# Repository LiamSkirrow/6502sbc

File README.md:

# 6502 🎉

A minimal implementation of a functional 6502-based system. It has everything that's needed to get going, including a 6522 VIA (for parallel ports/GPIO control) and a 6551 ACIA (for uart connection to a serial terminal).

## Pics
TODO, include screenshots of schematic and PCB. Can I render these automatically based on the current state of the schem/pcb in the repo?

## Memory Map
TODO

## Bootloader
ASM TODO

## Components
TODO

## Tutorial, how to get up and running
TODO, sourcing components, board bring-up, writing your own ASM snippets and loading them into ram via the bootloader+serial chip. How to write your own ISRs etc.

### Development Notes
- consider replacing zero-Ohm resistors with jumper headers, so I can place/replace them without a soldering iron
- add a jumper header to be able to switch between powering the board directly via a 5V USB cable, and an LM7805 linear reg. Three way jumper header to make it impossible to simultaneously select both options.
- rework memory map so that the ROM is only large enough to contain the minimal bootloader (+ a little extra just in case). We only need the ROM to be as large as the bootloader, since the RAM is where the user-code will be loaded into ready for execution, so minimise ROM and maximise RAM util.
  - perhaps rather than sacrifice a small but fixed amount of memory to the bootloader, why not think of a way to utilise the full 64kB RAM chip once the bootloader has completed. There would need to be some kind of dynamic bank-switching involved, possibly involving one output bit of the 6522 GPIO port to adjust the address decoding to no longer enable the ROM, instead always enabling the RAM (except obviously for when accessing the 6522/6551). So, when the bootloader completes and jumps to the starting address of the user program (in RAM), the first instructions should write to a special GPIO bit that switches out the default decode logic for another logic function that keeps the ROM disabled and RAM enabled. This way, we'd be able to utilise the full ROM space and then when its job is complete we could switch to utilising the full RAM space. So we don't need to use small, fixed regions of memory at any one time, instead using potentially the full capacity of the chip.

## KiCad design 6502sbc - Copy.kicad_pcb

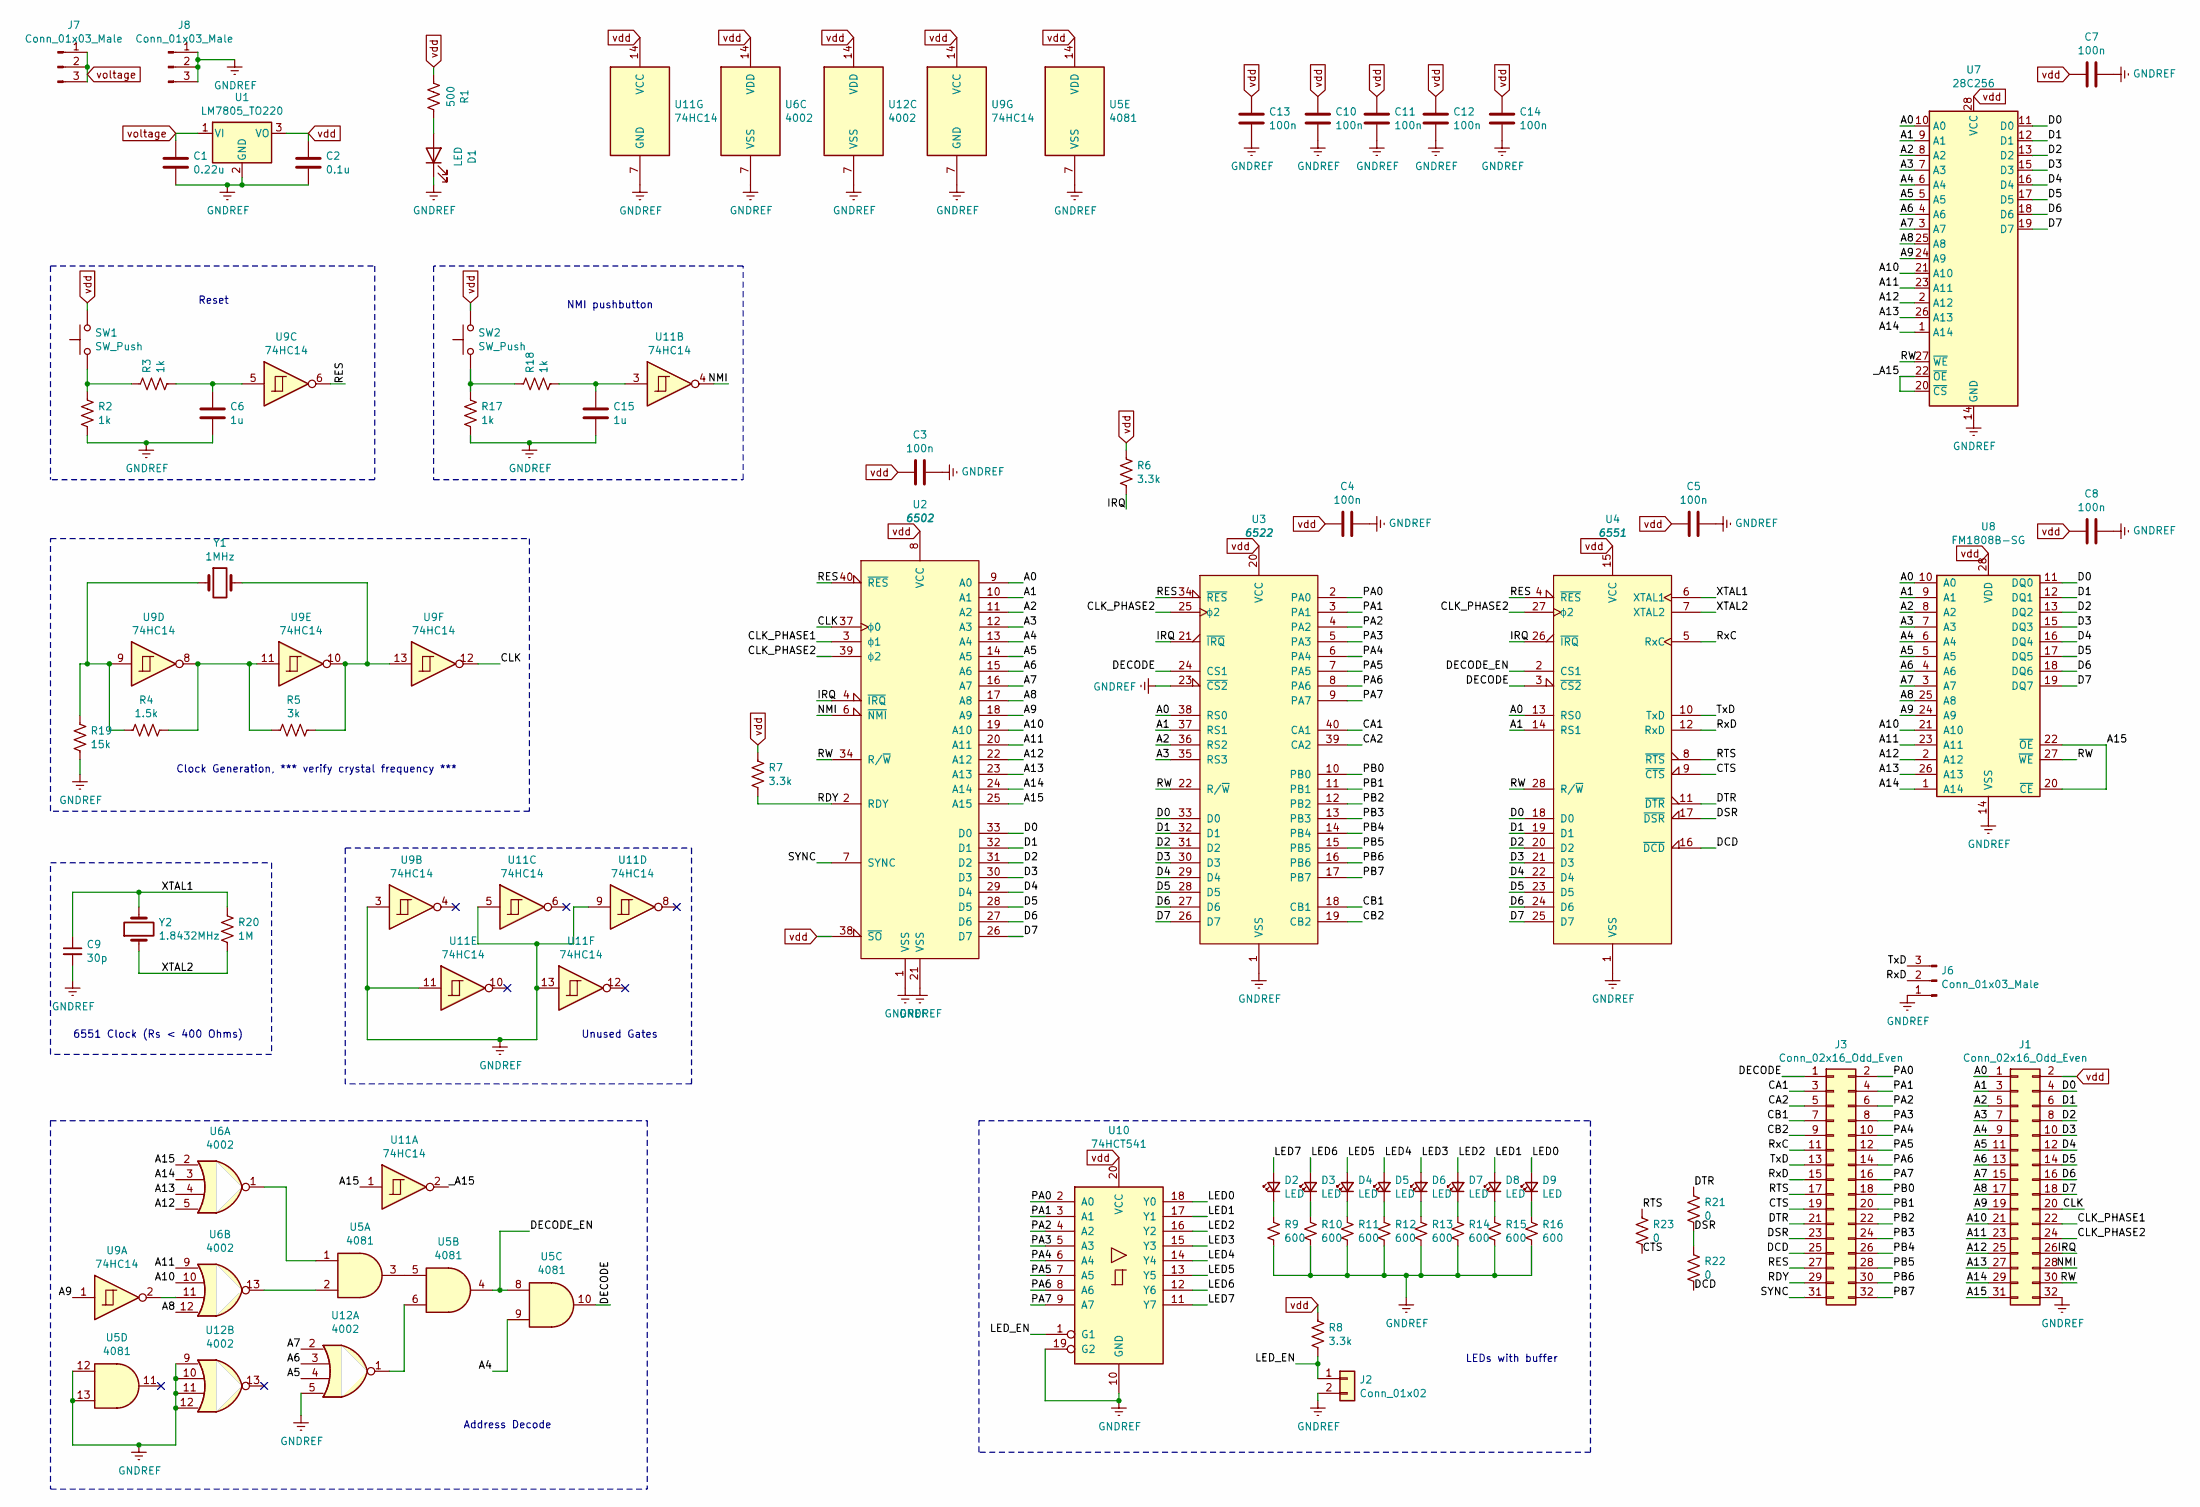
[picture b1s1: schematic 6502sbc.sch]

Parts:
C1: 0.22u; C_0805_2012Metric_Pad1.18x1.45mm_HandSolder
C2: 0.1u; C_0603_1608Metric_Pad1.08x0.95mm_HandSolder
C3, C4, C5, C7, C8, C10, C11, C12, C13, C14: 100n; C_0603_1608Metric_Pad1.08x0.95mm_HandSolder
C6, C15: 1u; C_0805_2012Metric_Pad1.18x1.45mm_HandSolder
C9: 30p; C_0805_2012Metric_Pad1.18x1.45mm_HandSolder
D1, D2, D3, D4, D5, D6, D7, D8, D9: LED; LED_0805_2012Metric_Pad1.15x1.40mm_HandSolder
J1, J3: Conn_02x16_Odd_Even; PinHeader_2x16_P2.54mm_Vertical
J2: Conn_01x02; PinHeader_1x02_P2.54mm_Vertical
J6, J7, J8: Conn_01x03_Male; PinHeader_1x03_P2.54mm_Vertical
R1: 500; R_0805_2012Metric_Pad1.20x1.40mm_HandSolder
R2, R3, R17, R18: 1k; R_0805_2012Metric_Pad1.20x1.40mm_HandSolder
R4: 1.5k; R_0805_2012Metric_Pad1.20x1.40mm_HandSolder
R5: 3k; R_0805_2012Metric_Pad1.20x1.40mm_HandSolder
R6, R7, R8: 3.3k; R_0805_2012Metric_Pad1.20x1.40mm_HandSolder
R9, R10, R11, R12, R13, R14, R15, R16: 600; R_0603_1608Metric_Pad1.05x0.95mm_HandSolder
R19: 15k; R_0805_2012Metric_Pad1.20x1.40mm_HandSolder
R20: 1M; R_0805_2012Metric_Pad1.20x1.40mm_HandSolder
R21, R22, R23: 0; R_0805_2012Metric_Pad1.20x1.40mm_HandSolder
SW1, SW2: SW_Push; SW_Push_1P1T_NO_6x6mm_H9.5mm
U1: LM7805_TO220; TO-220-3_Vertical
U2: 6502; DIP-40_W15.24mm
U3: 6522; DIP-40_W15.24mm
U4: 6551; DIP-28_W15.24mm
U5: 4081; SO-14_3.9x8.65mm_P1.27mm
U6, U12: 4002; SO-14_3.9x8.65mm_P1.27mm
U7: 28C256; DIP-28_W15.24mm
U8: FM1808B-SG; DIP-28_W15.24mm
U9, U11: 74HC14; SO-14_3.9x8.65mm_P1.27mm
U10: 74HCT541; SOIC-20W_7.5x12.8mm_P1.27mm
Y1: 1MHz; Resonator-2Pin_W6.0mm_H3.0mm
Y2: 1.8432MHz; Resonator-2Pin_W6.0mm_H3.0mm

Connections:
/A0: J1.1, U2.9 (A0), U3.38 (RS0), U4.13 (RS0), U7.10 (A0), U8.10 (A0)
/A1: J1.3, U2.10 (A1), U3.37 (RS1), U4.14 (RS1), U7.9 (A1), U8.9 (A1)
/A2: J1.5, U2.11 (A2), U3.36 (RS2), U7.8 (A2), U8.8 (A2)
/A3: J1.7, U2.12 (A3), U3.35 (RS3), U7.7 (A3), U8.7 (A3)
/A4: J1.9, U2.13 (A4), U5.9, U7.6 (A4), U8.6 (A4)
/A5: J1.11, U2.14 (A5), U7.5 (A5), U8.5 (A5), U12.4
/A6: J1.13, U2.15 (A6), U7.4 (A6), U8.4 (A6), U12.3
/A7: J1.15, U2.16 (A7), U7.3 (A7), U8.3 (A7), U12.2
/A8: J1.17, U2.17 (A8), U6.12, U7.25 (A8), U8.25 (A8)
/A9: J1.19, U2.18 (A9), U7.24 (A9), U8.24 (A9), U9.1
/A10: J1.21, U2.19 (A10), U6.10, U7.21 (A10), U8.21 (A10)
/A11: J1.23, U2.20 (A11), U6.9, U7.23 (A11), U8.23 (A11)
/A12: J1.25, U2.22 (A12), U6.5, U7.2 (A12), U8.2 (A12)
/A13: J1.27, U2.23 (A13), U6.4, U7.26 (A13), U8.26 (A13)
/A14: J1.29, U2.24 (A14), U6.3, U7.1 (A14), U8.1 (A14)
/A15: J1.31, U2.25 (A15), U6.2, U8.20 (~CE~), U8.22 (~OE~), U11.1
/CA1: J3.3, U3.40 (CA1)
/CA2: J3.5, U3.39 (CA2)
/CB1: J3.7, U3.18 (CB1)
/CB2: J3.9, U3.19 (CB2)
/CLK: J1.20, U2.37 (ϕ0), U9.12
/CLK_PHASE1: J1.22, U2.3 (ϕ1)
/CLK_PHASE2: J1.24, U2.39 (ϕ2), U3.25 (ϕ2), U4.27 (ϕ2)
/CTS: J3.19, R23.2, U4.9 (~CTS)
/D0: J1.4, U2.33 (D0), U3.33 (D0), U4.18 (D0), U7.11 (D0), U8.11 (DQ0)
/D1: J1.6, U2.32 (D1), U3.32 (D1), U4.19 (D1), U7.12 (D1), U8.12 (DQ1)
/D2: J1.8, U2.31 (D2), U3.31 (D2), U4.20 (D2), U7.13 (D2), U8.13 (DQ2)
/D3: J1.10, U2.30 (D3), U3.30 (D3), U4.21 (D3), U7.15 (D3), U8.15 (DQ3)
/D4: J1.12, U2.29 (D4), U3.29 (D4), U4.22 (D4), U7.16 (D4), U8.16 (DQ4)
/D5: J1.14, U2.28 (D5), U3.28 (D5), U4.23 (D5), U7.17 (D5), U8.17 (DQ5)
/D6: J1.16, U2.27 (D6), U3.27 (D6), U4.24 (D6), U7.18 (D6), U8.18 (DQ6)
/D7: J1.18, U2.26 (D7), U3.26 (D7), U4.25 (D7), U7.19 (D7), U8.19 (DQ7)
/DCD: J3.25, R22.2, U4.16 (~DCD)
/DECODE: J3.1, U3.24 (CS1), U4.3 (~CS2), U5.10
/DECODE_EN: U4.2 (CS1), U5.4, U5.8
/DSR: J3.23, R21.2, R22.1, U4.17 (~DSR)
/DTR: J3.21, R21.1, U4.11 (~DTR)
/IRQ: J1.26, R6.2, U2.4 (~IRQ), U3.21 (~IRQ), U4.26 (~IRQ)
/LED0: D9.2 (A), U10.18 (Y0)
/LED1: D8.2 (A), U10.17 (Y1)
/LED2: D7.2 (A), U10.16 (Y2)
/LED3: D6.2 (A), U10.15 (Y3)
/LED4: D5.2 (A), U10.14 (Y4)
/LED5: D4.2 (A), U10.13 (Y5)
/LED6: D3.2 (A), U10.12 (Y6)
/LED7: D2.2 (A), U10.11 (Y7)
/LED_EN: J2.1, R8.2, U10.1 (G1)
/NMI: J1.28, U2.6 (~NMI), U11.4
/PA0: J3.2, U3.2 (PA0), U10.2 (A0)
/PA1: J3.4, U3.3 (PA1), U10.3 (A1)
/PA2: J3.6, U3.4 (PA2), U10.4 (A2)
/PA3: J3.8, U3.5 (PA3), U10.5 (A3)
/PA4: J3.10, U3.6 (PA4), U10.6 (A4)
/PA5: J3.12, U3.7 (PA5), U10.7 (A5)
/PA6: J3.14, U3.8 (PA6), U10.8 (A6)
/PA7: J3.16, U3.9 (PA7), U10.9 (A7)
/PB0: J3.18, U3.10 (PB0)
/PB1: J3.20, U3.11 (PB1)
/PB2: J3.22, U3.12 (PB2)
/PB3: J3.24, U3.13 (PB3)
/PB4: J3.26, U3.14 (PB4)
/PB5: J3.28, U3.15 (PB5)
/PB6: J3.30, U3.16 (PB6)
/PB7: J3.32, U3.17 (PB7)
/RDY: J3.29, R7.2, U2.2 (RDY)
/RES: J3.27, U2.40 (~RES), U3.34 (~RES), U4.4 (~RES), U9.6
/RTS: J3.17, R23.1, U4.8 (~RTS)
/RW: J1.30, U2.34 (R/~W), U3.22 (R/~W), U4.28 (R/~W), U7.27 (~WE), U8.27 (~WE~)
/RxC: J3.11, U4.5 (RxC)
/RxD: J3.15, J6.2, U4.12 (RxD)
/SYNC: J3.31, U2.7 (SYNC)
/TxD: J3.13, J6.3, U4.10 (TxD)
/XTAL1: C9.1, R20.1, U4.6 (XTAL1), Y2.2
/XTAL2: R20.2, U4.7 (XTAL2), Y2.1
/_A15: U7.20 (~CS), U7.22 (~OE), U11.2
GNDREF: C1.2, C2.2, C3.1, C4.1, C5.1, C6.1, C7.1, C8.1, C9.2, C10.2, C11.2, C12.2, C13.2, C14.2, C15.1, D1.1 (K), J1.32, J2.2, J6.1, J8.1, J8.2, J8.3, R2.2, R9.2, R10.2, R11.2, R12.2, R13.2, R14.2, R15.2, R16.2, R17.2, R19.2, U1.2 (GND), U2.1 (VSS), U2.21 (VSS), U3.1 (VSS), U3.23 (~CS2), U4.1 (VSS), U5.7 (VSS), U5.12, U5.13, U6.7 (VSS), U7.14 (GND), U8.14 (VSS), U9.3, U9.7 (GND), U10.10 (GND), U10.19 (G2), U11.5, U11.7 (GND), U11.9, U11.11, U11.13, U12.5, U12.7 (VSS), U12.9, U12.10, U12.11, U12.12
unnamed: C6.2, R3.2, U9.5
unnamed: C15.2, R18.2, U11.3
unnamed: D1.2 (A), R1.1
unnamed: D2.1 (K), R9.1
unnamed: D3.1 (K), R10.1
unnamed: D4.1 (K), R11.1
unnamed: D5.1 (K), R12.1
unnamed: D6.1 (K), R13.1
unnamed: D7.1 (K), R14.1
unnamed: D8.1 (K), R15.1
unnamed: D9.1 (K), R16.1
unnamed: R2.1, R3.1, SW1.1
unnamed: R4.1, R5.2, U9.8, U9.11
unnamed: R5.1, U9.10, U9.13, Y1.2
unnamed: R17.1, R18.1, SW2.1
unnamed: R4.2, R19.1, U9.9, Y1.1
unnamed: U5.1, U6.1
unnamed: U5.2, U6.13
unnamed: U5.3, U5.5
unnamed: U6.11, U9.2
unnamed: U5.6, U12.1
vdd: C2.1, C3.2, C4.2, C5.2, C7.2, C8.2, C10.1, C11.1, C12.1, C13.1, C14.1, J1.2, R1.2, R6.1, R7.1, R8.1, SW1.2, SW2.2, U1.3 (VO), U2.8 (VCC), U2.38 (~SO), U3.20 (VCC), U4.15 (VCC), U5.14 (VDD), U6.14 (VDD), U7.28 (VCC), U8.28 (VDD), U9.14 (VCC), U10.20 (VCC), U11.14 (VCC), U12.14 (VDD)
voltage: C1.1, J7.1, J7.2, J7.3, U1.1 (VI)

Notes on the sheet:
Reset
Address Decode
Clock Generation, *** verify crystal frequency ***
6551 Clock (Rs < 400 Ohms)
LEDs with buffer
NMI pushbutton
Unused Gates

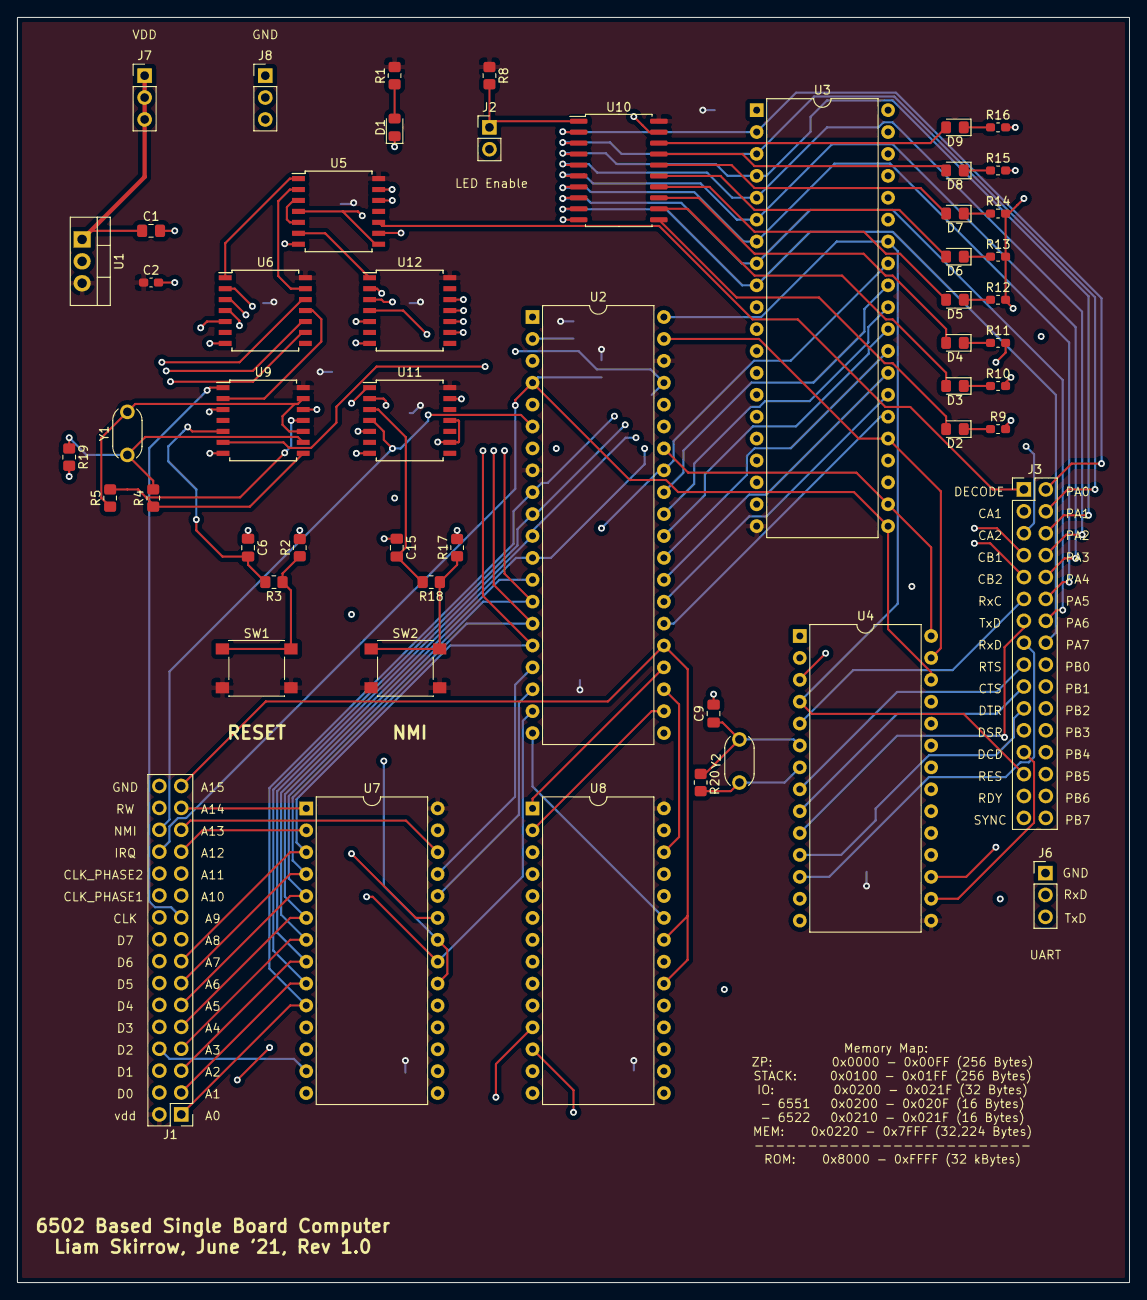
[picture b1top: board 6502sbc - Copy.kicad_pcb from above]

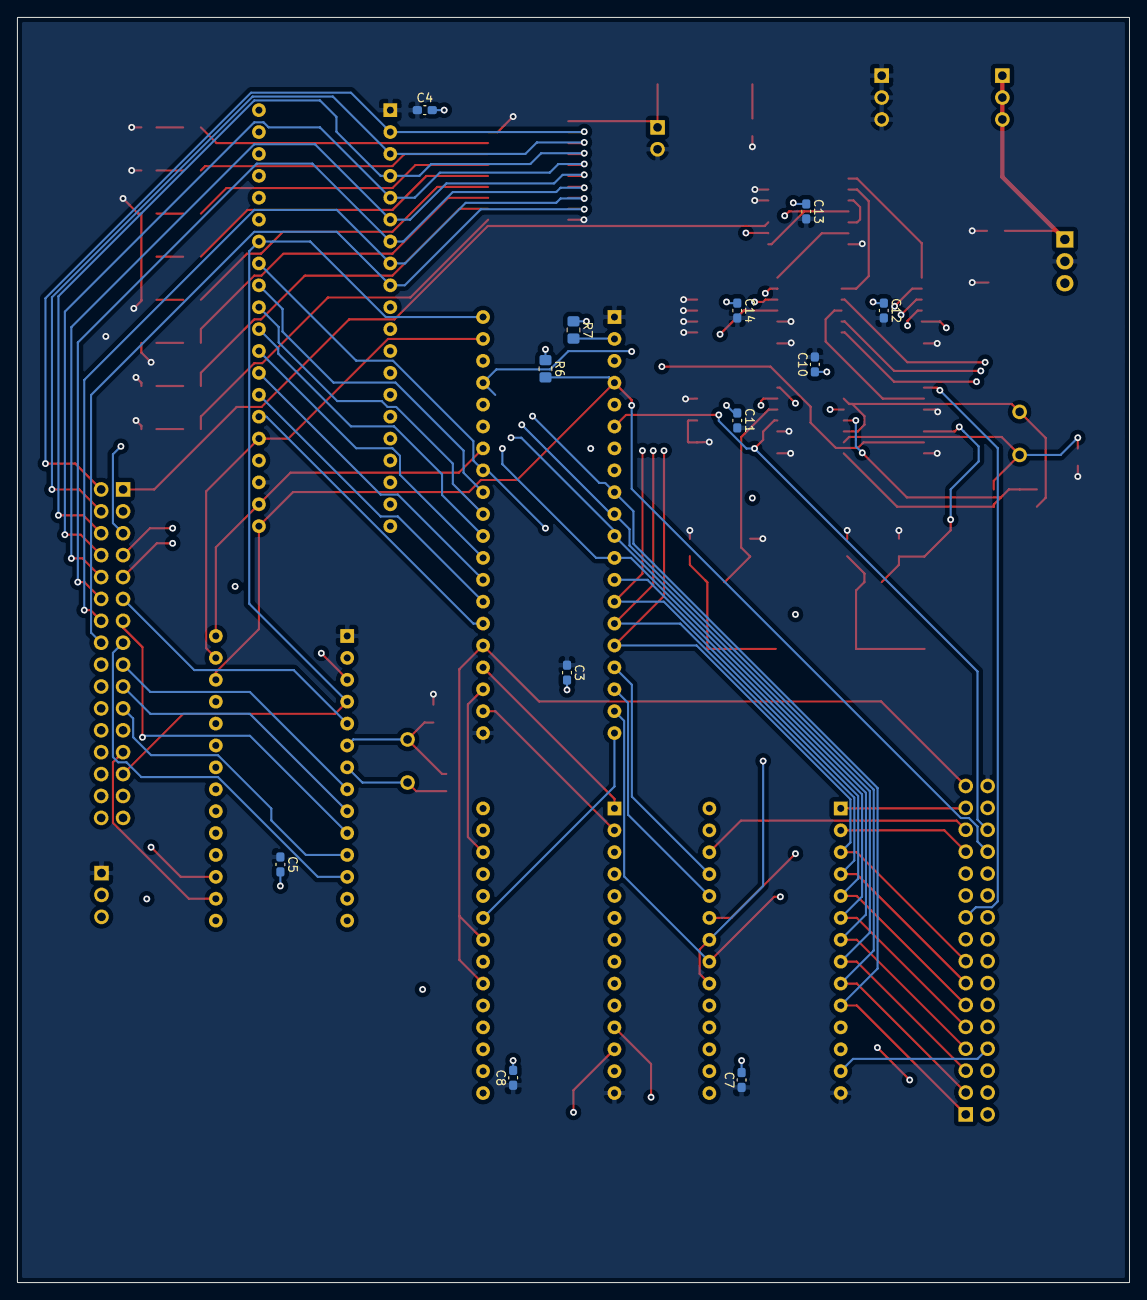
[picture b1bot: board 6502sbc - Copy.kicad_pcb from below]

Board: 4 copper layers, 129.0 x 146.8 mm, 66 parts (12 on the bottom side), 99 nets.

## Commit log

2026-03-15 Create README.md for 6502 project
    Add initial README with project overview and TODOs
2026-03-15 Update README with development notes
    Added development notes regarding hardware modifications and memory optimization.
2026-03-15 Update section title and add screenshot note
    Shortened section title and clarified screenshot inclusion.
